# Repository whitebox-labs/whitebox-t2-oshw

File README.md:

model `T2.21 SMA`
# Whitebox T2 Mini MkII for Arduino

## Hardware repository

The Whitebox T2 Mini MkII is an Arduino Shield to easily connect and isolate Atlas Scientific EZO devices to an Arduino. The Whitebox T2 is Open Source Hardware and this is the public repository of the source files.

- Whitebox T2 user documentation: https://www.whiteboxes.ch/docs/tentacle/t2-mkII/#/
- Buy the Whitebox T2 here: https://www.whiteboxes.ch/shop/t2-mini-mk2/

Hardware source files licensed under [Creative Commons BY-SA 4.0](http://creativecommons.org/licenses/by-sa/4.0/)

Made with 

The Whitebox T2 Mini MkII hardware source is licensed under a
[Creative Commons Attribution-ShareAlike 4.0 International License][cc-by-sa].

[![CC BY-SA 4.0][cc-by-sa-image]][cc-by-sa]

[cc-by-sa]: http://creativecommons.org/licenses/by-sa/4.0/
[cc-by-sa-image]: https://licensebuttons.net/l/by-sa/4.0/88x31.png

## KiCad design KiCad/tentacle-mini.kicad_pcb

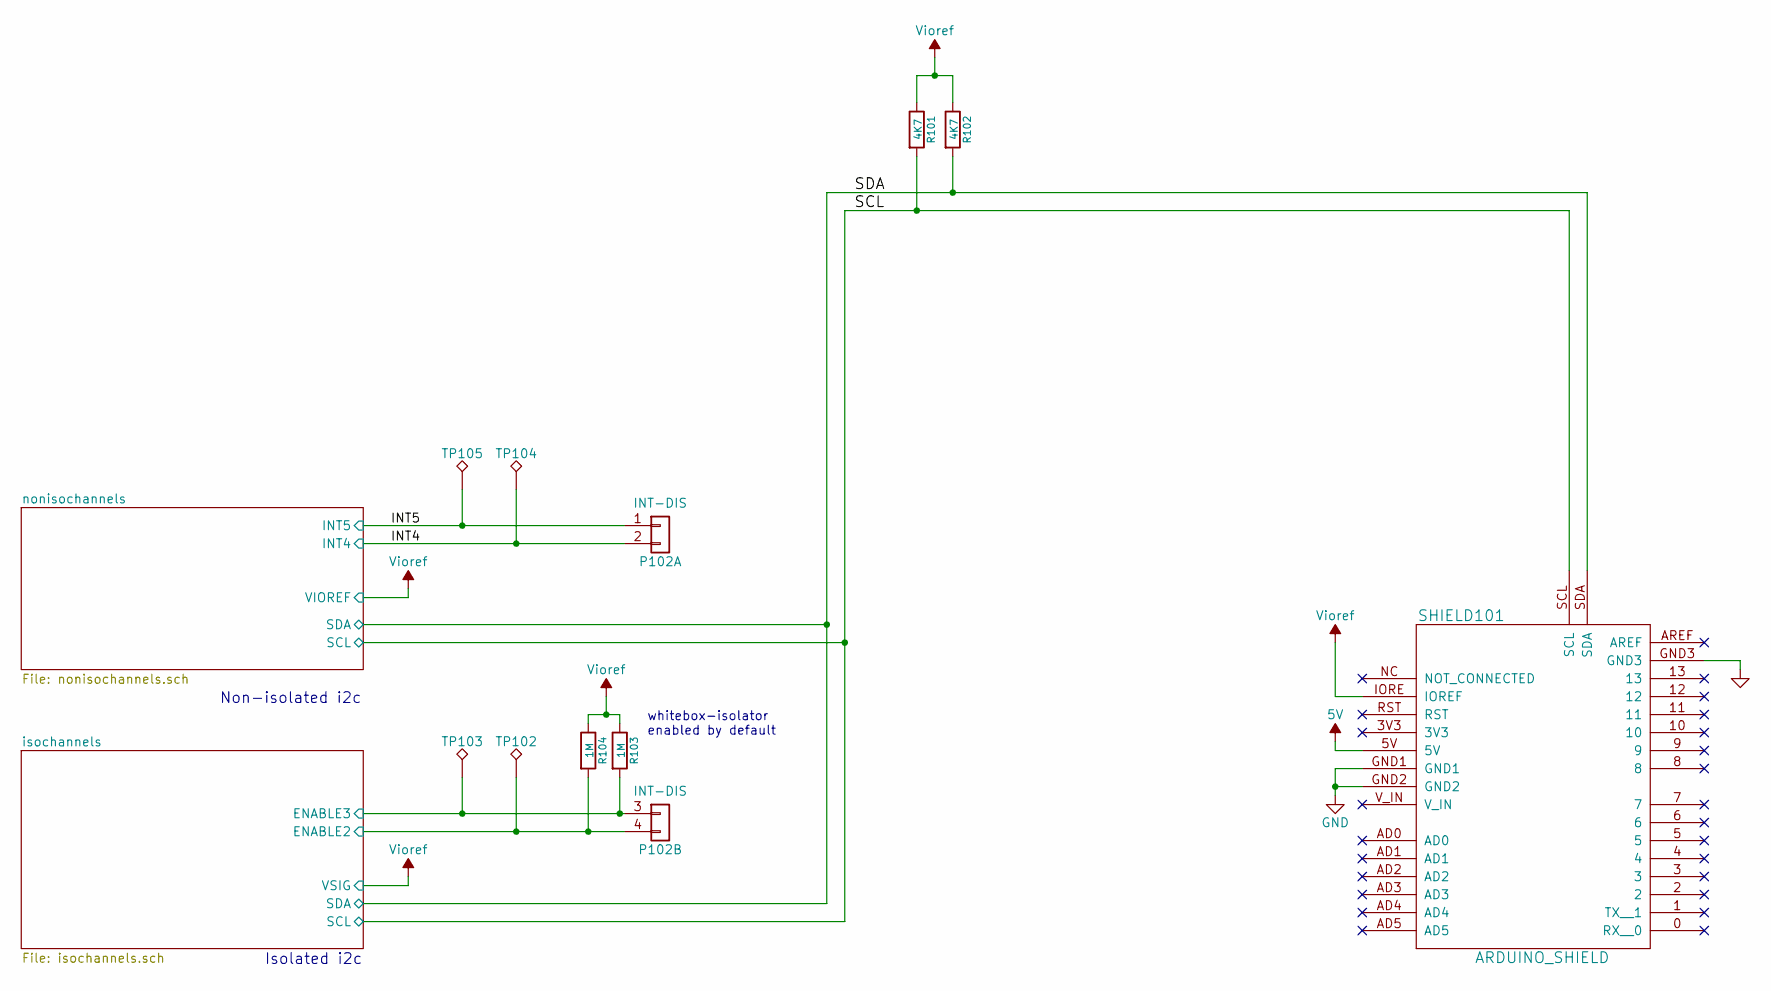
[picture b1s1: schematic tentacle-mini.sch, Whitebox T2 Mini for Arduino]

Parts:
P102: INT-DIS; WB-1x4-header-female-SMD
R101, R102: 4K7; WB-R-SMD-0402
R103, R104: 1M; WB-R-SMD-0402
SHIELD101: ARDUINO_SHIELD; WB-t2-shield
TP102, TP103, TP104, TP105: TestPoint; WB-testpoint

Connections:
5V: SHIELD101.5V; also elsewhere on the board
/INT4: P102.2 (Pin_4), TP104.1; also elsewhere on the board
/INT5: P102.1 (Pin_3), TP105.1; also elsewhere on the board
/SCL: R101.2, SHIELD101.SCL; also elsewhere on the board
/SDA: R102.2, SHIELD101.SDA; also elsewhere on the board
/isochannels/ENABLE2: P102.4, R104.2, TP102.1; also elsewhere on the board
/isochannels/ENABLE3: P102.3, R103.2, TP103.1; also elsewhere on the board
GND: SHIELD101.GND1, SHIELD101.GND2, SHIELD101.GND3; also elsewhere on the board
Vioref: R101.1, R102.1, R103.1, R104.1, SHIELD101.IORE (IOREF); also elsewhere on the board

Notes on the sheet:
Non-isolated i2c
Isolated i2c
whitebox-isolator enabled by default

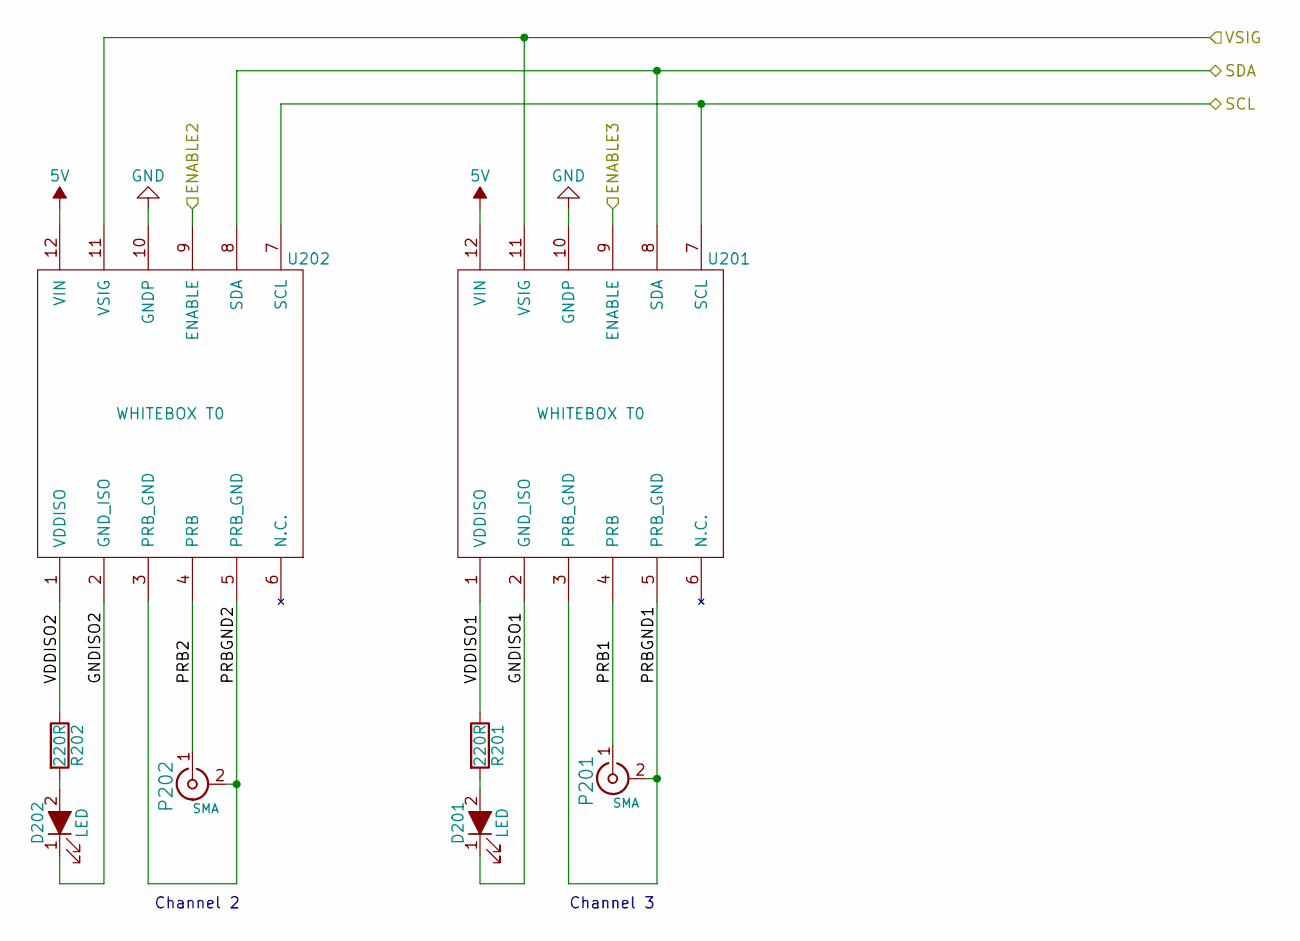
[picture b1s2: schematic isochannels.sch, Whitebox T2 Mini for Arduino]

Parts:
D201, D202: LED; WB-LED-G-SMD-0402
P201, P202: SMA; WB-SMA_EDGES_CORNER
R201, R202: 220R; WB-R-SMD-0402
U201, U202: WHITEBOX T0; WB-T0-isolator-temporary-bugfix

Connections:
5V: U201.12 (VIN), U202.12 (VIN); also elsewhere on the board
/SCL: U201.7 (SCL), U202.7 (SCL); also elsewhere on the board
/SDA: U201.8 (SDA), U202.8 (SDA); also elsewhere on the board
/isochannels/ENABLE2: U202.9 (ENABLE); also elsewhere on the board
/isochannels/ENABLE3: U201.9 (ENABLE); also elsewhere on the board
/isochannels/GNDISO1: D201.1 (K), U201.2 (GND_ISO)
/isochannels/GNDISO2: D202.1 (K), U202.2 (GND_ISO)
/isochannels/PRB1: P201.1 (In), U201.4 (PRB)
/isochannels/PRB2: P202.1 (In), U202.4 (PRB)
/isochannels/PRBGND1: P201.2 (Ext), U201.3 (PRB_GND), U201.5 (PRB_GND)
/isochannels/PRBGND2: P202.2 (Ext), U202.3 (PRB_GND), U202.5 (PRB_GND)
/isochannels/VDDISO1: R201.1, U201.1 (VDDISO)
/isochannels/VDDISO2: R202.1, U202.1 (VDDISO)
GND: U201.10 (GNDP), U202.10 (GNDP); also elsewhere on the board
unnamed: D201.2 (A), R201.2
unnamed: D202.2 (A), R202.2
Vioref: U201.11 (VSIG), U202.11 (VSIG); also elsewhere on the board

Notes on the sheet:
Channel 3
Channel 2

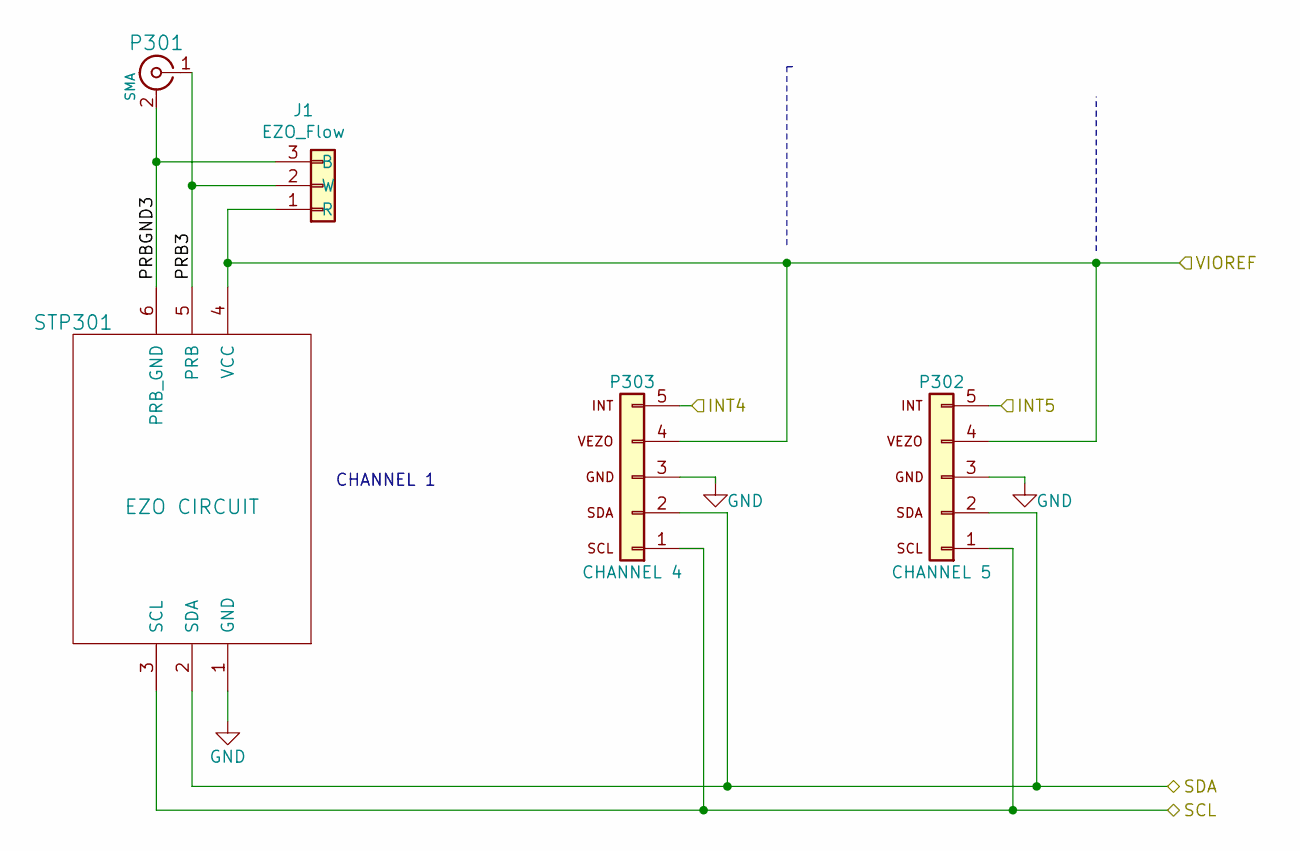
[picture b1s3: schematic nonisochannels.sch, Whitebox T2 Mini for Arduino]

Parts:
J1: EZO_Flow; WB-1x3-pin-header-handsolder
P301: SMA; WB-SMA_EDGES_CORNER
P302: CHANNEL 5; WB-1x5-header-male-SMD
P303: CHANNEL 4; WB-1x5-header-male-SMD
STP301: EZO CIRCUIT; WB-EZO-RL

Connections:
/INT4: P303.5; also elsewhere on the board
/INT5: P302.5; also elsewhere on the board
/SCL: P302.1, P303.1, STP301.3 (SCL); also elsewhere on the board
/SDA: P302.2, P303.2, STP301.2 (SDA); also elsewhere on the board
/nonisochannels/PRB3: J1.2 (W), P301.1 (In), STP301.5 (PRB)
/nonisochannels/PRBGND3: J1.3 (B), P301.2 (Ext), STP301.6 (PRB_GND)
GND: P302.3, P303.3, STP301.1 (GND); also elsewhere on the board
Vioref: J1.1 (R), P302.4, P303.4, STP301.4 (VCC); also elsewhere on the board

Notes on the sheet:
CHANNEL 1

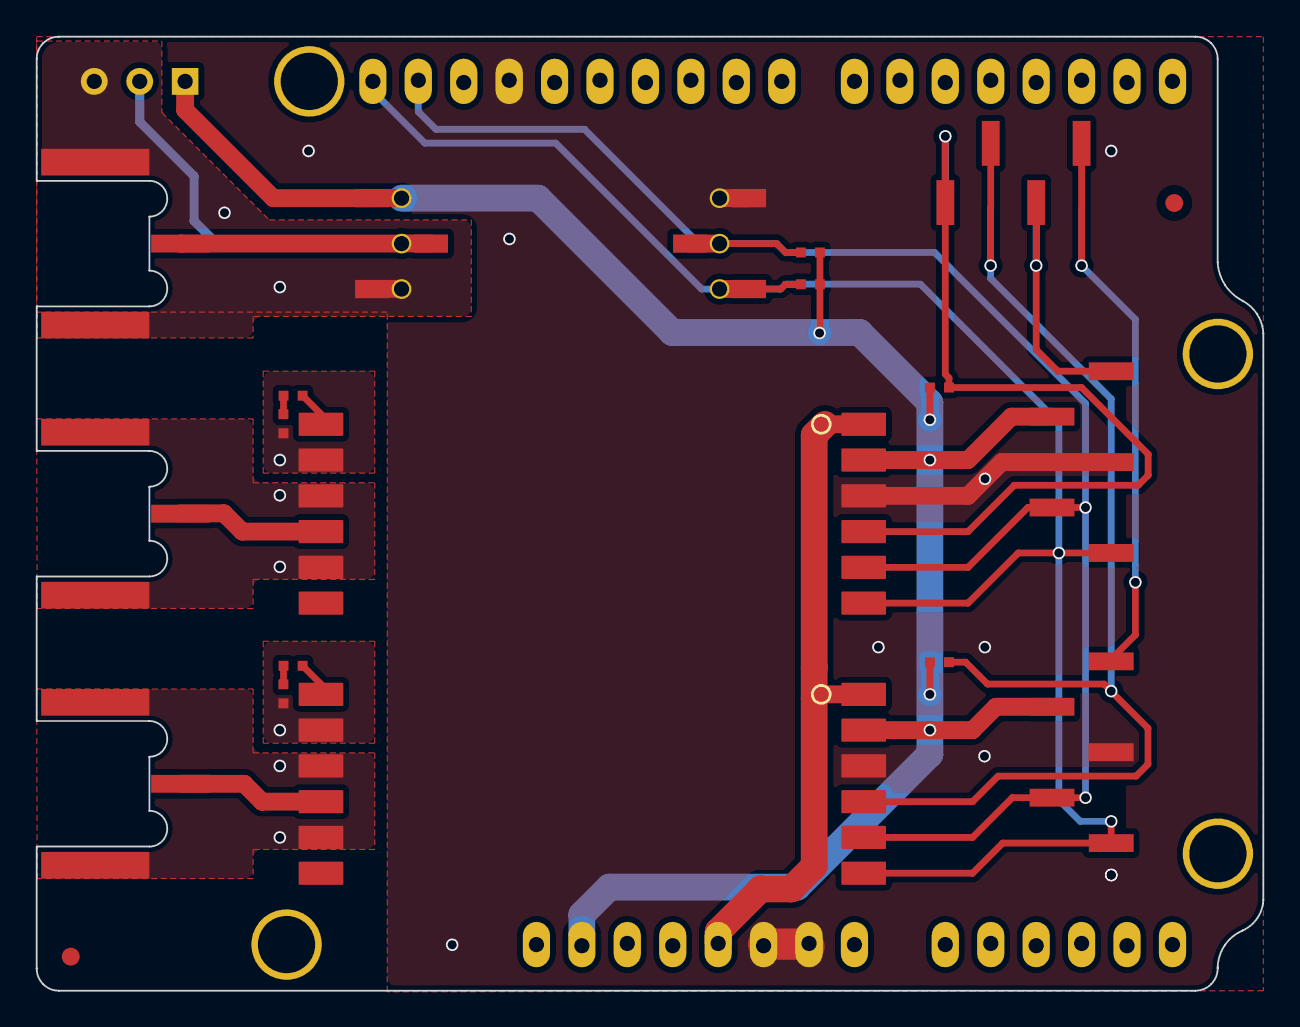
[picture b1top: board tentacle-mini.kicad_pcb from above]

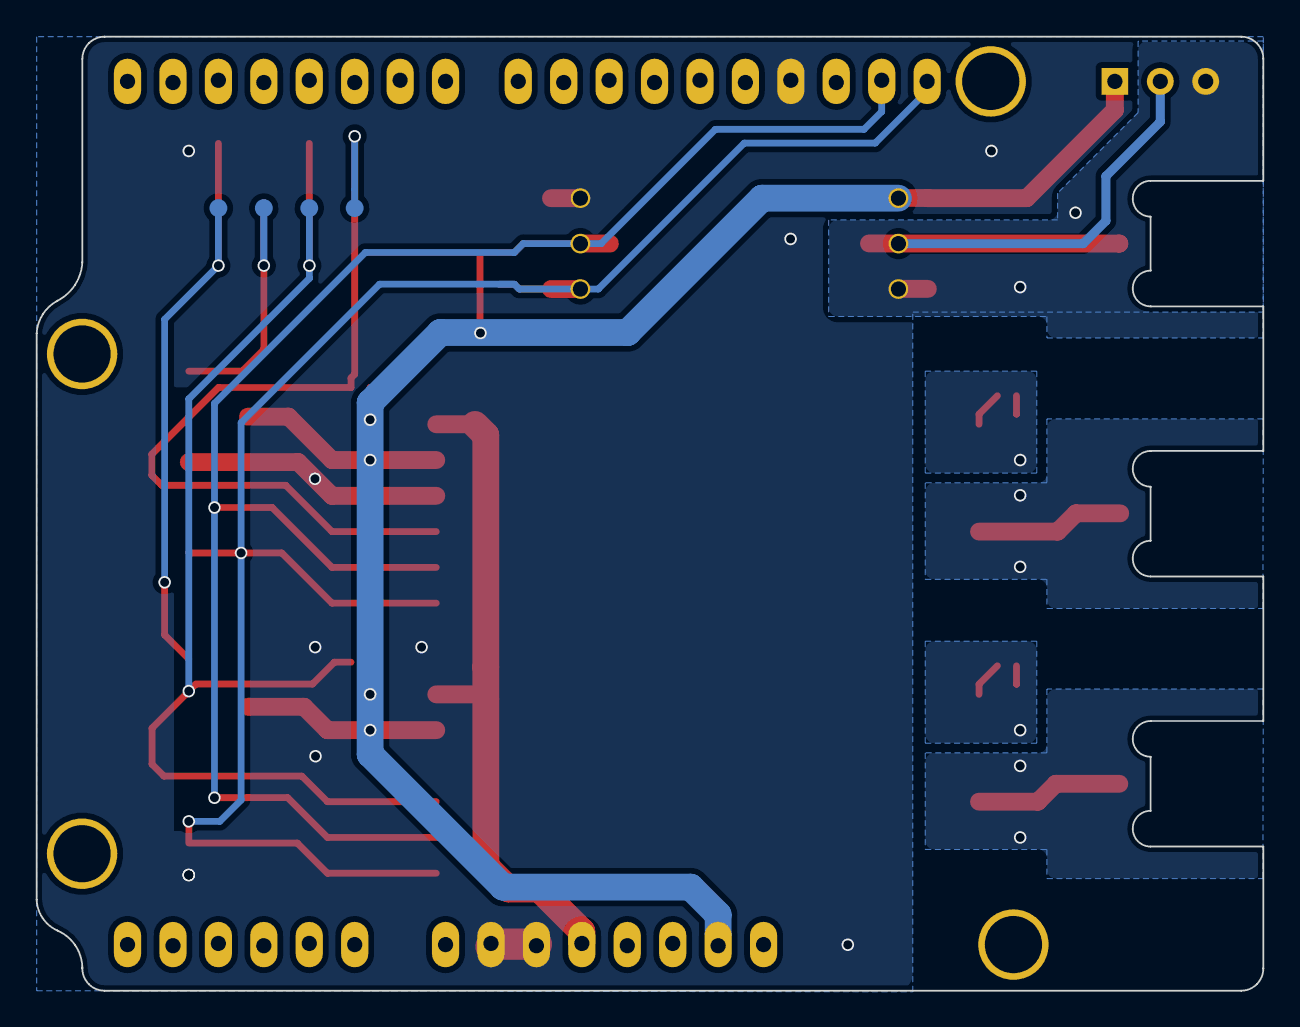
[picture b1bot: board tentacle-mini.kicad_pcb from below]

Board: 2 copper layers, 68.6 x 53.3 mm, 25 parts (4 on the bottom side), 21 nets.

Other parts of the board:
fiducial: FIDUCIAL 1; WB-fiducial_1mm
fiducial#2: FIDUCIAL 2; WB-fiducial_1mm

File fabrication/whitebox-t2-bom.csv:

Description,Reference,Qty, Value, Footprint
T0 Whitebox Isolator,U201 U202 ,2,,tentacle:WB-T0-isolator
LED for T0 Whitebox Isolator “on”,D201 D202 ,2,20mA,tentacle:WB-LED-G-SMD-0402
"Resistor Size 0402, 1%, 1/8W   (i2c)",R101 R102 ,2,4.7K,tentacle:WB-R-SMD-0402
"Resistor Size 0402, 1%, 1/8W   (enable)",R103 R104 ,2,1M,tentacle:WB-R-SMD-0402
"Resistor Size 0402,  1%, 1/16W  (LED)",R201 R202 ,2,270,tentacle:WB-R-SMD-0402
SMD  connector for Atlas Stamp,STP301 ,2,1x3 pin,tentacle:WB-EZO-RL
BNC connector for sensor,P201 P202 P301 ,3,BNC,tentacle:WB-BNC
SMD female connector for disable,P102 ,1,1x4 pin,tentacle:WB-1x4-header-female-SMD
SMD male connector for channels 4 and 5,P302 P303,2,1x5 pin,tentacle:WB-1x5-header-male-SMD
1x6-pin female header .1inch THT,SHIELD101,1,0.1”,tentacle-mini:WB-t2-shield
1x8-pin female header .1inch THT,SHIELD101,2,0.1”,tentacle-mini:WB-t2-shield
1x10-pin female header .1inch THT,SHIELD101,1,0.1”,tentacle-mini:WB-t2-shield

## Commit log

2020-12-08 added whitebox t2 mkII hardware source files
2020-12-08 added BOM in csv format + zipped STEP file
2020-12-08 added rendering to readme
2020-12-08 added licence to readme
2020-12-08 Create LICENSE
2021-05-03 updated bom, preview, readme, schematic pdf for SMA
2021-05-03 update for SMA
2021-11-10 Update README.md
    https://forum.kicad.info/t/warning-avoid-all-links-to-kicad-pcb-org-use-kicad-org/31521

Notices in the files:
KiCad/isochannels.sch:
This work is licensed under a Creative Commons
